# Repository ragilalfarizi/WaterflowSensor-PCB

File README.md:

# PCB design of The Wattermatters
## Schematic

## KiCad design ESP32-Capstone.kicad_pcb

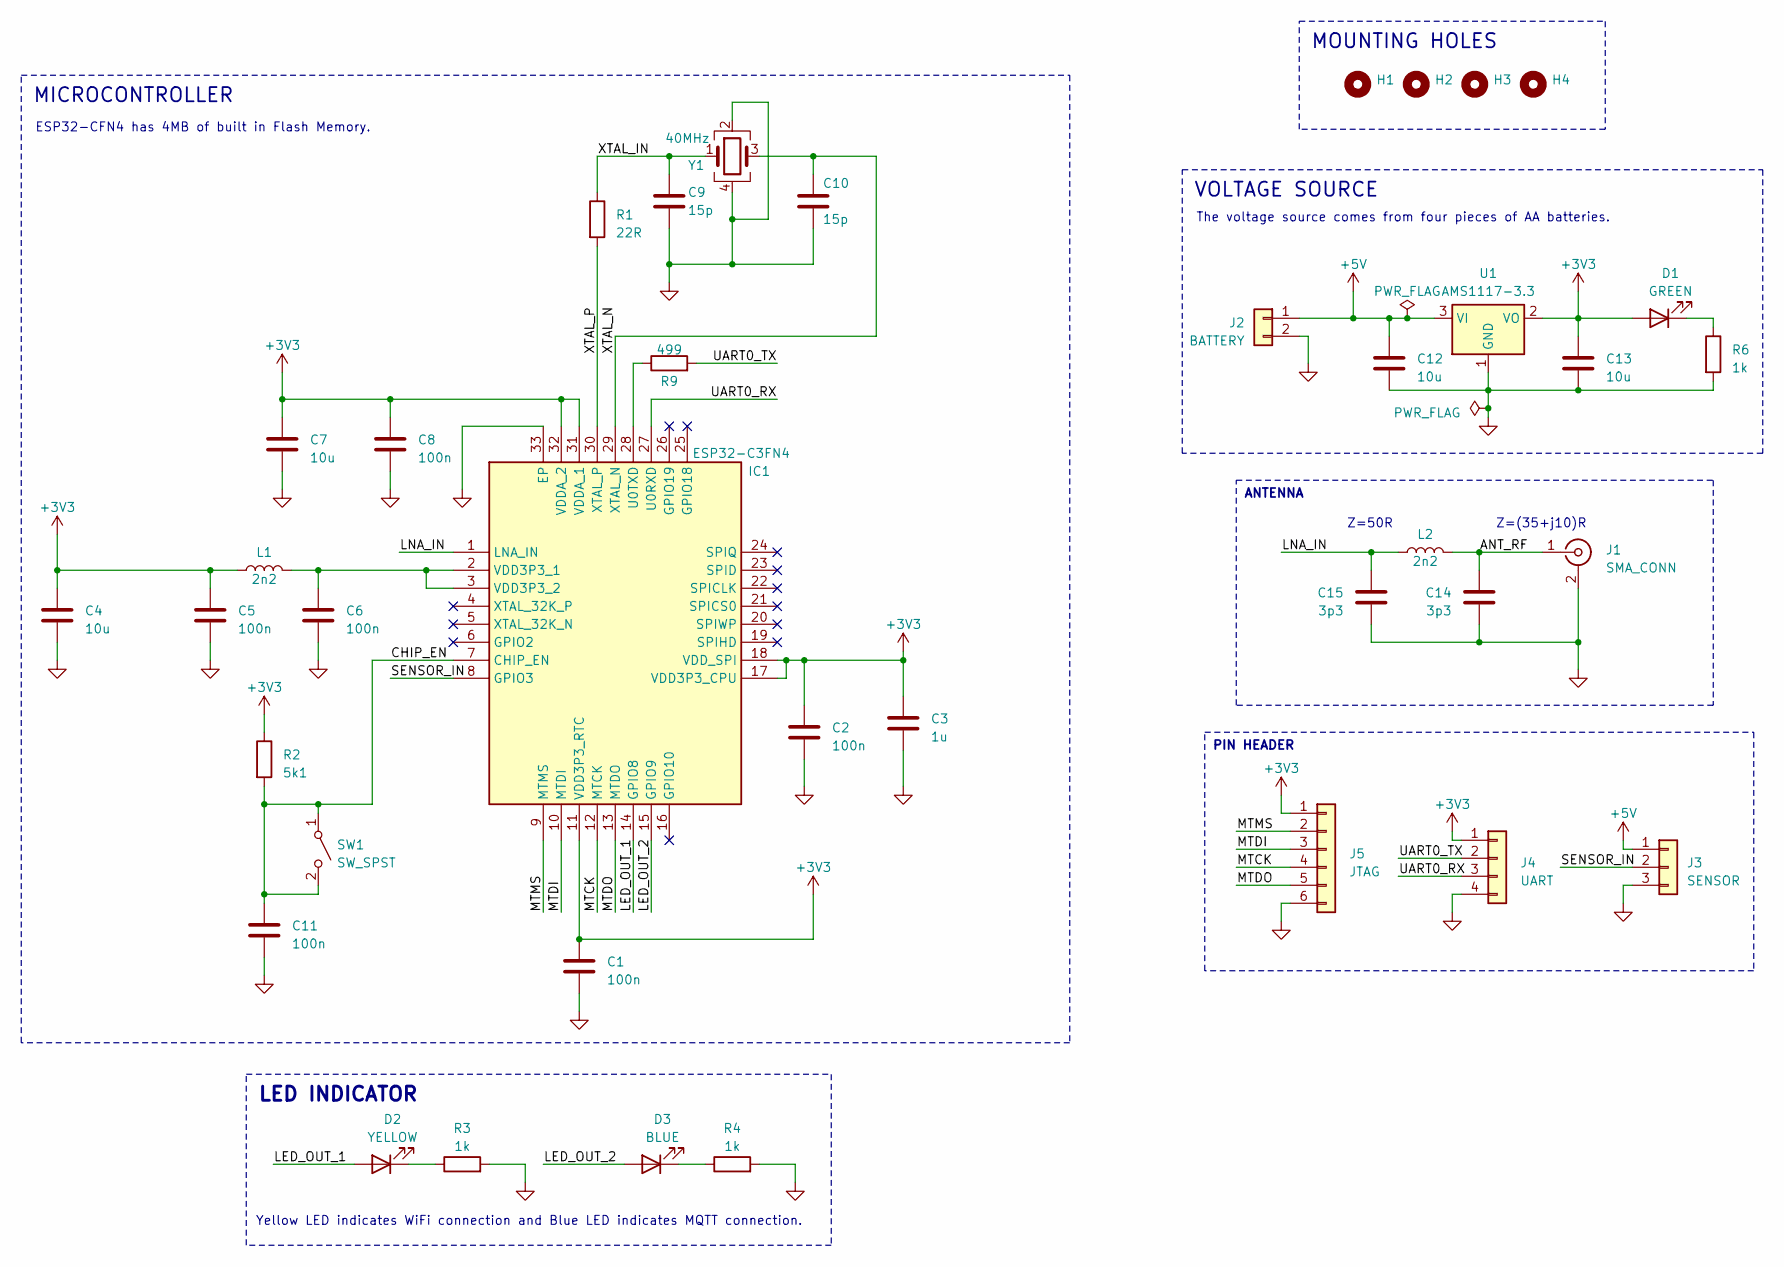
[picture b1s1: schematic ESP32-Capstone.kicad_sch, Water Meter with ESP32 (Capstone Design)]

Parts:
C1, C2, C5, C6, C8, C11: 100n; C_0402_1005Metric
C3: 1u; C_0402_1005Metric
C4, C7, C12, C13: 10u; C_0402_1005Metric
C9, C10: 15p; C_0402_1005Metric
C14, C15: 3p3; C_0402_1005Metric
D1: GREEN; LED_0603_1608Metric
D2: YELLOW; LED_0603_1608Metric
D3: BLUE; LED_0603_1608Metric
H1, H2, H3, H4: MountingHole; MountingHole_2.2mm_M2_ISO14580
IC1: ESP32-C3FN4; QFN50P500X500X90-33N-D; Manufacturer_Part_Number ESP32-C3FN4; Mouser Part Number 356-ESP32-C3FN4
J1: SMA_CONN; SMA_Molex_73251-1153_EdgeMount_Horizontal
J2: BATTERY; JST_EH_S2B-EH_1x02_P2.50mm_Horizontal
J3: SENSOR; JST_EH_S3B-EH_1x03_P2.50mm_Horizontal
J4: UART; PinHeader_1x04_P2.54mm_Vertical
J5: JTAG; PinHeader_1x06_P2.54mm_Vertical
L1, L2: 2n2; L_0402_1005Metric
R1: 22R; R_0402_1005Metric
R2: 5k1; R_0402_1005Metric
R3, R4, R6: 1k; R_0402_1005Metric
R9: 499; R_0402_1005Metric
SW1: SW_SPST; SW_SPST_B3U-1000P
U1: AMS1117-3.3; SOT-223-3_TabPin2
Y1: 40MHz; Crystal_SMD_SeikoEpson_FA238-4Pin_3.2x2.5mm

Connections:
+3V3: C1.1, C2.1, C3.1, C4.1, C5.1, C7.1, C8.1, C13.1, D1.2 (A), IC1.11 (VDD3P3_RTC), IC1.17 (VDD3P3_CPU), IC1.18 (VDD_SPI), IC1.31 (VDDA_1), IC1.32 (VDDA_2), J4.1, J5.1, L1.1, R2.1, U1.2 (VO)
+5V: C12.1, J2.1, J3.1, U1.3 (VI)
/ANT_RF: C14.1, J1.1 (In), L2.1
/CHIP_EN: C11.1, IC1.7 (CHIP_EN), R2.2, SW1.1 (A), SW1.2 (B)
/LED_OUT_1: D2.2 (A), IC1.14 (GPIO8)
/LED_OUT_2: D3.2 (A), IC1.15 (GPIO9)
/LNA_IN: C15.1, IC1.1 (LNA_IN), L2.2
/MTCK: IC1.12 (MTCK), J5.4
/MTDI: IC1.10 (MTDI), J5.3
/MTDO: IC1.13 (MTDO), J5.5
/MTMS: IC1.9 (MTMS), J5.2
/SENSOR_IN: IC1.8 (GPIO3), J3.2
/UART0_RX: IC1.27 (U0RXD), J4.3
/UART0_TX: J4.2, R9.2
/XTAL_IN: C9.1, R1.1, Y1.1
/XTAL_N: C10.1, IC1.29 (XTAL_N), Y1.3
/XTAL_P: IC1.30 (XTAL_P), R1.2
GND: C1.2, C2.2, C3.2, C4.2, C5.2, C6.2, C7.2, C8.2, C9.2, C10.2, C11.2, C12.2, C13.2, C14.2, C15.2, IC1.33 (EP), J1.2 (Ext), J2.2, J3.3, J4.4, J5.6, R3.2, R4.2, R6.2, U1.1 (GND), Y1.2, Y1.4
unnamed: D1.1 (K), R6.1
unnamed: D2.1 (K), R3.1
unnamed: D3.1 (K), R4.1
unnamed: IC1.28 (U0TXD), R9.1
unnamed: C6.1, IC1.2 (VDD3P3_1), IC1.3 (VDD3P3_2), L1.2

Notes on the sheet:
VOLTAGE SOURCE
ANTENNA
PIN HEADER
LED INDICATOR
MICROCONTROLLER
MOUNTING HOLES
Z=50R
The voltage source comes from four pieces of AA batteries.
Yellow LED indicates WiFi connection and Blue LED indicates MQTT connection.
ESP32-CFN4 has 4MB of built in Flash Memory.
Z=(35+j10)R

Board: 2 copper layers, 39 parts (0 on the bottom side), 23 nets, no tracks yet.

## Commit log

2023-07-04 feat: add Power Supply, also UART and JTAG label
2023-07-08 feat: add Antenna, JTAG, and UART. Schematic V1 is done.
2023-07-08 feat: add schematic images
2023-07-08 fix: change background color on schematic capture
2023-07-08 fix: change the schematic image path
2023-07-09 fix: update schematic picture
